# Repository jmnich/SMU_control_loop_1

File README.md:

# SMU_control_loop_1

Control loop module for HTBlog Source Measure Unit

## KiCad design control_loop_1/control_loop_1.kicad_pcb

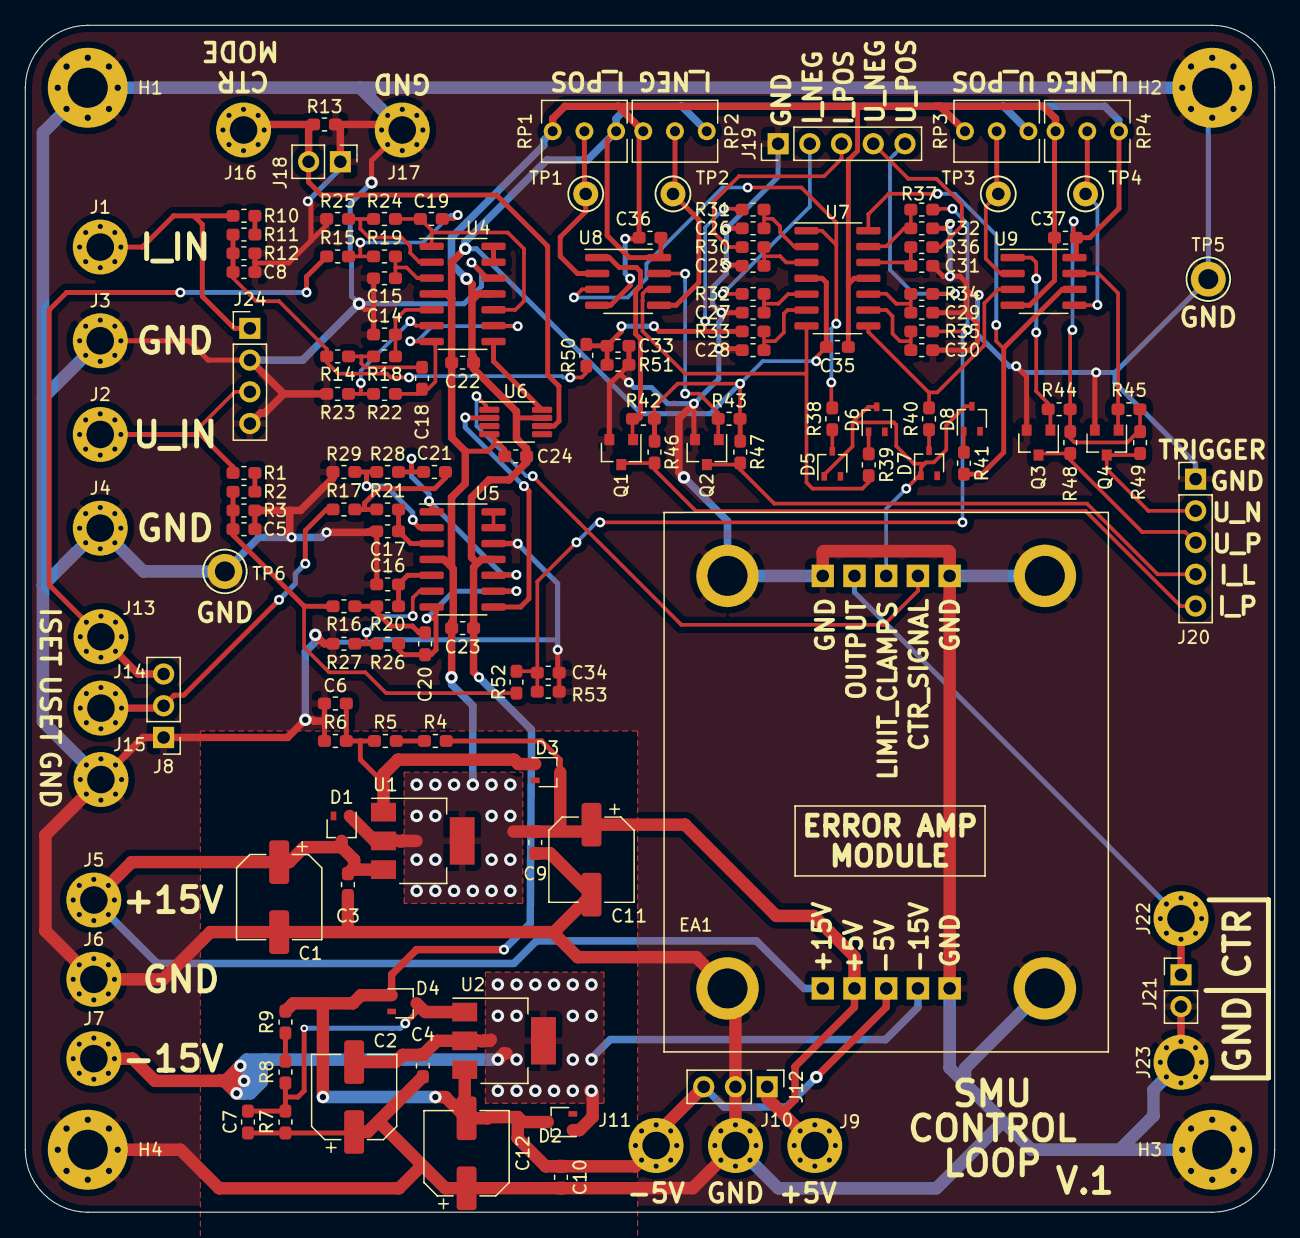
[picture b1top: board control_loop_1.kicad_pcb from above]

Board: 2 copper layers, 100.0 x 95.0 mm, 148 parts (0 on the bottom side), 75 nets.

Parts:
C1, C2, C11, C12: 56u 25V; CP_Elec_6.3x5.9
C3, C4, C6, C7, C9, C10: 1u; C_0603_1608Metric_Pad1.05x0.95mm_HandSolder
C5, C8, C18, C19, C20, C21: 1n; C_0603_1608Metric_Pad1.05x0.95mm_HandSolder
C14, C15, C16, C17: 100p; C_0603_1608Metric_Pad1.05x0.95mm_HandSolder
C22, C23, C24, C35, C36, C37: 100n; C_0603_1608Metric_Pad1.05x0.95mm_HandSolder
C25, C26, C27, C28, C29, C30, C31, C32: 10n; C_0603_1608Metric_Pad1.05x0.95mm_HandSolder
C33, C34: DNP; C_0603_1608Metric_Pad1.05x0.95mm_HandSolder
D1, D2, D3, D4, D5, D6, D7, D8: BAT54WFILMY; SOT-323_SC-70
EA1: err_amp_module_1
H1, H2, H3, H4: MountingHole_Pad; MountingHole_3.2mm_M3_Pad_Via
J1: I_MEAS; MountingHole_2.2mm_M2_Pad_Via
J2: U_MEAS; MountingHole_2.2mm_M2_Pad_Via
J3, J4, J6, J10, J15, J17, J23: GND; MountingHole_2.2mm_M2_Pad_Via
J5: +15V; MountingHole_2.2mm_M2_Pad_Via
J7: -15V; MountingHole_2.2mm_M2_Pad_Via
J8: SET_CONN; PinHeader_1x03_P2.54mm_Vertical
J9: +5V; MountingHole_2.2mm_M2_Pad_Via
J11: -5V; MountingHole_2.2mm_M2_Pad_Via
J12: POW_OUT; PinHeader_1x03_P2.54mm_Vertical
J13: I_SET; MountingHole_2.2mm_M2_Pad_Via
J14: U_SET; MountingHole_2.2mm_M2_Pad_Via
J16: CTR_MODE; MountingHole_2.2mm_M2_Pad_Via
J18: CTR_MODE; PinHeader_1x02_P2.54mm_Vertical
J19: Limit_conn; PinHeader_1x05_P2.54mm_Vertical
J20: Trig_conn; PinHeader_1x05_P2.54mm_Vertical
J21: CTR_SIG; PinHeader_1x02_P2.54mm_Vertical
J22: CTR_SIG_OUT; MountingHole_2.2mm_M2_Pad_Via
J24: Conn_01x04; PinHeader_1x04_P2.54mm_Vertical
Q1, Q2, Q3, Q4: 2N7002BK; SOT-23
R1, R2, R3, R10, R11, R12: 20k 0.1%; R_0603_1608Metric_Pad1.05x0.95mm_HandSolder
R4, R5, R8, R9, R13: 20k 1%; R_0603_1608Metric_Pad1.05x0.95mm_HandSolder
R6, R7: 120k 1%; R_0603_1608Metric_Pad1.05x0.95mm_HandSolder
R14, R15, R16, R17: 9.09k 0.1%; R_0603_1608Metric_Pad1.05x0.95mm_HandSolder
R18, R19, R20, R21: 306k 0.1%; R_0603_1608Metric_Pad1.05x0.95mm_HandSolder
R22, R24, R26, R28, R38, R39, R40, R41, R50, R52: 0R; R_0603_1608Metric_Pad1.05x0.95mm_HandSolder
R23, R25, R27, R29, R51, R53: DNP; R_0603_1608Metric_Pad1.05x0.95mm_HandSolder
R30, R32, R34, R36: 16k; R_0603_1608Metric_Pad1.05x0.95mm_HandSolder
R31, R33, R35, R37: 1k; R_0603_1608Metric_Pad1.05x0.95mm_HandSolder
R42, R43, R44, R45, R46, R47, R48, R49: 10k; R_0603_1608Metric_Pad1.05x0.95mm_HandSolder
RP1, RP2, RP3, RP4: 10k; Potentiometer_Vishay_T73XW_Horizontal
TP1, TP2, TP3, TP4: TestPoint; TestPoint_Keystone_5000-5004_Miniature
TP5, TP6: TestPoint; TestPoint_Keystone_5010-5014_Multipurpose
U1: LM317EMPX/NOPB; SOT-223-3_TabPin2
U2: LM337IMP/NOPB; SOT-223-3_TabPin2
U4, U5, U7: OPA1679IDR; SOIC-14_3.9x8.7mm_P1.27mm
U6: DG469EQ-T1-E3; MSOP-8_3x3mm_P0.65mm
U8, U9: LM393BIDR; SOIC-8_3.9x4.9mm_P1.27mm

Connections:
+5V: C9.2, C11.1, C22.1, C23.1, C24.1, C35.1, C36.1, C37.1, D1.1, D3.3, EA1.2, J9.1, J12.1, R4.1, R42.2, R43.2, R44.2, R45.2, R46.2, R47.2, R48.2, R49.2, RP1.1, RP2.1, RP3.1, RP4.1, U1.2, U4.4, U5.4, U6.4, U7.4, U8.8, U9.8
+15V: C1.1, C3.2, D1.3, EA1.1, J5.1, U1.3
-5V: C10.2, C12.2, C22.2, C23.2, C24.2, C35.2, C36.2, C37.2, D2.3, D4.1, EA1.3, J11.1, J12.3, R9.1, RP1.3, RP2.3, RP3.3, RP4.3, U2.3, U4.11, U5.11, U6.7, U7.11, U8.4, U9.4
-15V: C2.2, C4.2, D2.1, EA1.4, J7.1, U2.2
/CTR_MODE: J16.1, J18.2, R13.1, U6.6
/I_MEAS: C8.2, R11.2, R12.1, R14.2, R50.1
/UI_clamps/CONTROL_SIG_OUT: EA1.7, U6.1
/UI_clamps/I_SET: J8.3, J13.1, R15.2
/UI_clamps/U_SET: J8.2, J14.1, R17.2
/U_MEAS: C5.2, R2.2, R3.1, R16.2, R52.1
/limit_clamps/I_L_LIMIT: J19.2, R32.2
/limit_clamps/I_L_TRIG: J20.4, Q2.3, R47.1
/limit_clamps/I_P_LIMIT: J19.3, R30.2
/limit_clamps/I_P_TRIG: J20.5, Q1.3, R46.1
/limit_clamps/I_SIG: C33.1, R31.2, R33.2, R50.2, R51.1
/limit_clamps/LIMIT_CLAMPS_OUT: D5.1, D6.3, D7.1, D8.3, EA1.8
/limit_clamps/U_L_LIMIT: J19.4, R36.2
/limit_clamps/U_L_TRIG: J20.2, Q4.3, R49.1
/limit_clamps/U_P_LIMIT: J19.5, R34.2
/limit_clamps/U_P_TRIG: J20.3, Q3.3, R48.1
/limit_clamps/U_SIG: C34.1, R35.2, R37.2, R52.2, R53.1
GND: C1.2, C2.1, C3.1, C4.1, C5.1, C6.1, C7.1, C8.1, C9.1, C10.1, C11.2, C12.1, C14.2, C15.2, C16.2, C17.2, C25.2, C26.2, C27.2, C28.2, C29.2, C30.2, C31.2, C32.2, C33.2, C34.2, EA1.5, EA1.6, EA1.10, EA1.11, H1.1, H2.1, H3.1, H4.1, J3.1, J4.1, J6.1, J8.1, J10.1, J12.2, J15.1, J17.1, J18.1, J19.1, J20.1, J21.2, J23.1, J24.2, J24.4, Q1.2, Q2.2, Q3.2, Q4.2, R3.2, R6.2, R7.2, R12.2, R13.2, R23.1, R25.1, R27.1, R29.1, R51.2, R53.2, TP5.1, TP6.1, U4.12, U5.12
unnamed: C6.2, D3.1, R5.2, R6.1, U1.1
unnamed: C7.2, D4.3, R7.1, R8.2, U2.1
unnamed: C14.1, R18.1, U4.5
unnamed: C15.1, R19.1, U4.3
unnamed: C16.1, R20.1, U5.5
unnamed: C17.1, R21.1, U5.3
unnamed: C18.1, R22.2, U4.7, U4.9
unnamed: C18.2, R14.1, R18.2
unnamed: C19.1, R24.2, U4.1, U4.10
unnamed: C19.2, R15.1, R19.2
unnamed: C20.1, R26.2, U5.7, U5.9
unnamed: C20.2, R16.1, R20.2
unnamed: C21.1, R28.2, U5.1, U5.10
unnamed: C21.2, R17.1, R21.2
unnamed: C25.1, R30.1, U7.3
unnamed: C26.1, R31.1, U7.2
unnamed: C27.1, R32.1, U7.5
unnamed: C28.1, R33.1, U7.6
unnamed: C29.1, R34.1, U7.10
unnamed: C30.1, R35.1, U7.9
unnamed: C31.1, R36.1, U7.12
unnamed: C32.1, R37.1, U7.13
unnamed: D5.3, R38.1
unnamed: D6.1, R39.1
unnamed: D7.3, R40.1
unnamed: D8.1, R41.1
unnamed: EA1.9, J21.1, J22.1
unnamed: J1.1, J24.1, R10.1
unnamed: J2.1, J24.3, R1.1
unnamed: Q1.1, R42.1, U8.1
unnamed: Q2.1, R43.1, U8.7
unnamed: Q3.1, R44.1, U9.1
unnamed: Q4.1, R45.1, U9.7
unnamed: R1.2, R2.1
unnamed: R4.2, R5.1
unnamed: R8.1, R9.2
unnamed: R10.2, R11.1
unnamed: R22.1, R23.2, U4.6
unnamed: R24.1, R25.2, U4.2
unnamed: R26.1, R27.2, U5.6
unnamed: R28.1, R29.2, U5.2
unnamed: R38.2, U7.1, U8.3
unnamed: R39.2, U7.7, U8.6
unnamed: R40.2, U7.8, U9.3
unnamed: R41.2, U7.14, U9.6
unnamed: RP1.2, TP1.1, U8.2
unnamed: RP2.2, TP2.1, U8.5
unnamed: RP3.2, TP3.1, U9.2
unnamed: RP4.2, TP4.1, U9.5
unnamed: U4.8, U6.8
unnamed: U4.13, U4.14
unnamed: U5.8, U6.2
unnamed: U5.13, U5.14

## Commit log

2020-10-17 image upload
2020-10-18 fixed diodes orientation
    negative volt regulator - reversed diodes fixed
2020-10-27 production files
